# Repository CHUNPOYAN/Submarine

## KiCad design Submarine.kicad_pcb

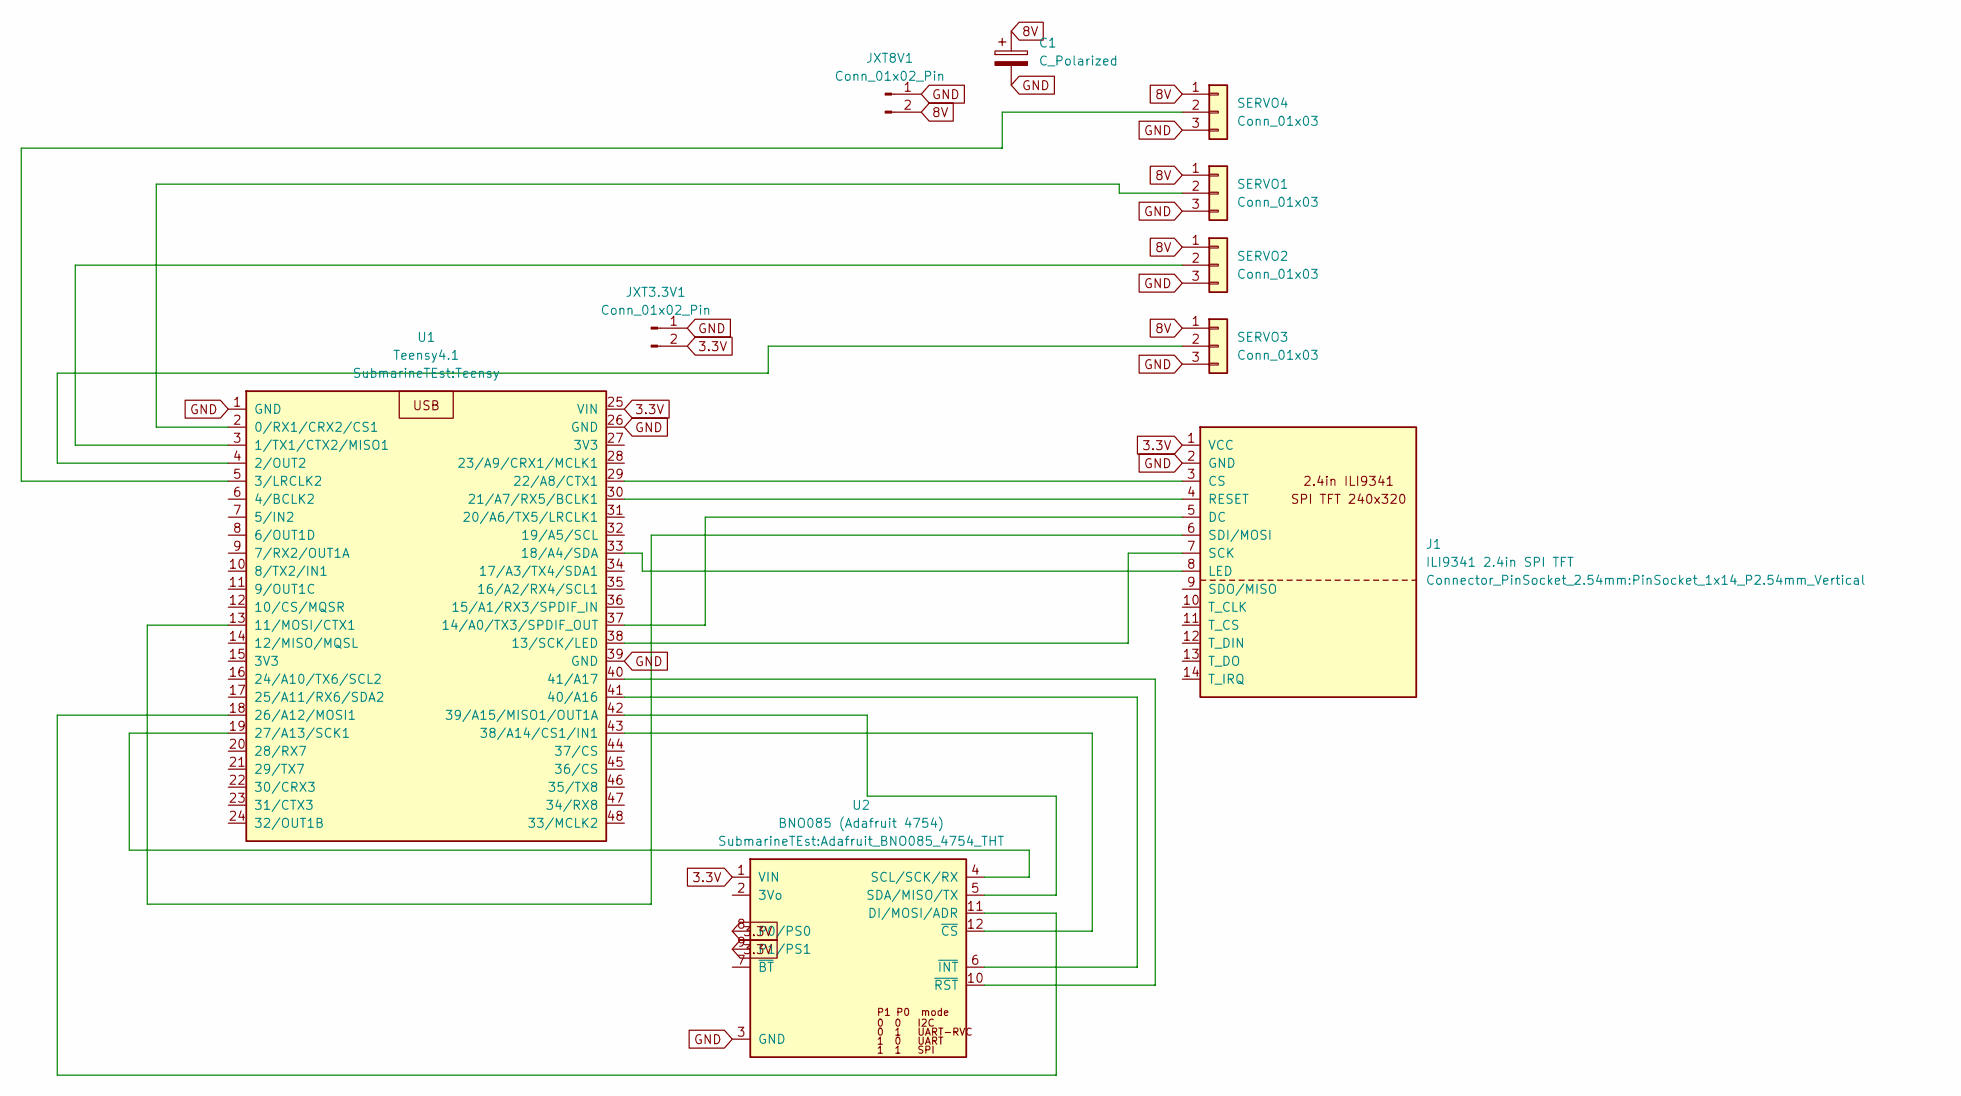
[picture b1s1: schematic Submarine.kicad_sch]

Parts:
C1: C_Polarized; CP_Radial_D10.0mm_P5.00mm
J1: ILI9341 2.4in SPI TFT; PinSocket_1x14_P2.54mm_Vertical
JXT3.3V1, JXT8V1: Conn_01x02_Pin; AMASS_XT60-M_1x02_P7.20mm_Vertical
SERVO1, SERVO2, SERVO3, SERVO4: Conn_01x03; SolderWire-0.5sqmm_1x03_P4.6mm_D0.9mm_OD2.1mm
U1: Teensy4.1; Teensy
U2: BNO085 (Adafruit 4754); Adafruit_BNO085_4754_THT

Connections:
3.3V: J1.1 (VCC), JXT3.3V1.2, U1.25 (VIN), U2.1 (VIN), U2.8 (P0/PS0), U2.9 (P1/PS1)
8V: C1.1, JXT8V1.2, SERVO1.1, SERVO2.1, SERVO3.1, SERVO4.1
GND: C1.2, J1.2 (GND), JXT3.3V1.1, JXT8V1.1, SERVO1.3, SERVO2.3, SERVO3.3, SERVO4.3, U1.1 (GND), U1.26 (GND), U1.39 (GND), U2.3 (GND)
unnamed: J1.3 (CS), U1.29 (22/A8/CTX1)
unnamed: J1.5 (DC), U1.37 (14/A0/TX3/SPDIF_OUT)
unnamed: J1.8 (LED), U1.33 (18/A4/SDA)
unnamed: J1.4 (RESET), U1.30 (21/A7/RX5/BCLK1)
unnamed: J1.7 (SCK), U1.38 (13/SCK/LED)
unnamed: J1.6 (SDI/MOSI), U1.13 (11/MOSI/CTX1)
unnamed: SERVO1.2, U1.2 (0/RX1/CRX2/CS1)
unnamed: SERVO2.2, U1.3 (1/TX1/CTX2/MISO1)
unnamed: SERVO3.2, U1.4 (2/OUT2)
unnamed: SERVO4.2, U1.5 (3/LRCLK2)
unnamed: U1.18 (26/A12/MOSI1), U2.11 (DI/MOSI/ADR)
unnamed: U1.19 (27/A13/SCK1), U2.4 (SCL/SCK/RX)
unnamed: U1.43 (38/A14/CS1/IN1), U2.12 (~CS)
unnamed: U1.42 (39/A15/MISO1/OUT1A), U2.5 (SDA/MISO/TX)
unnamed: U1.41 (40/A16), U2.6 (~INT)
unnamed: U1.40 (41/A17), U2.10 (~RST)

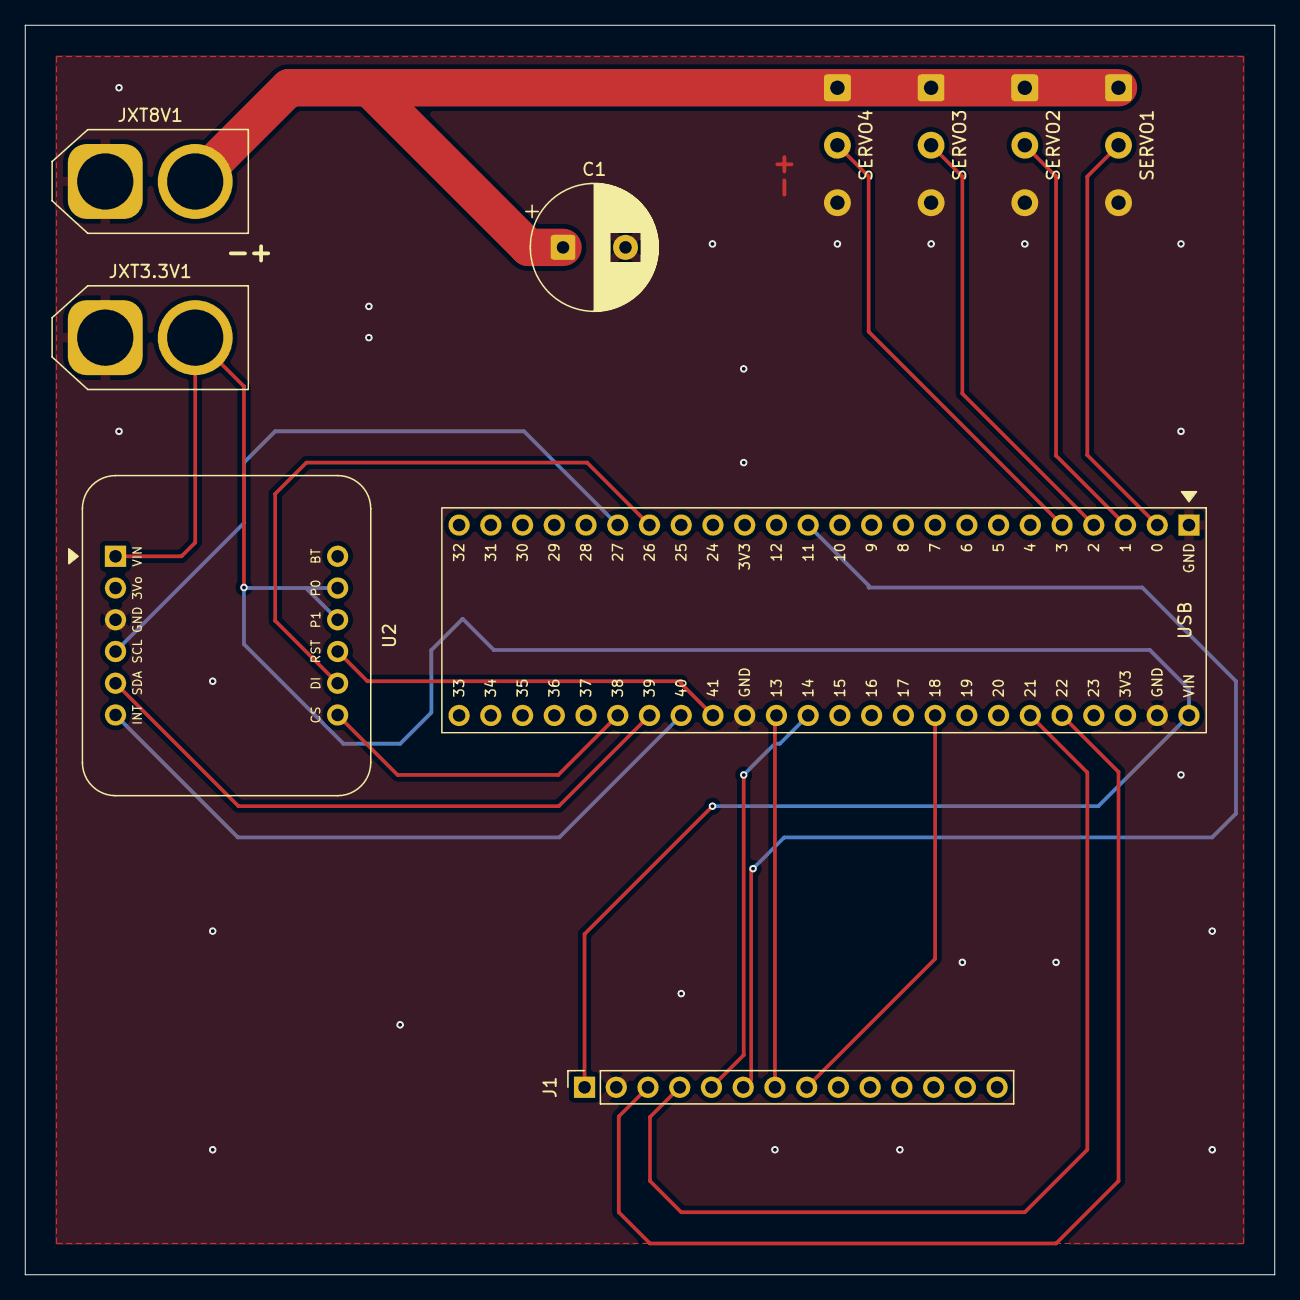
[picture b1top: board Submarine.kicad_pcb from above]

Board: 2 copper layers, 100.0 x 100.0 mm, 10 parts (0 on the bottom side), 19 nets.
